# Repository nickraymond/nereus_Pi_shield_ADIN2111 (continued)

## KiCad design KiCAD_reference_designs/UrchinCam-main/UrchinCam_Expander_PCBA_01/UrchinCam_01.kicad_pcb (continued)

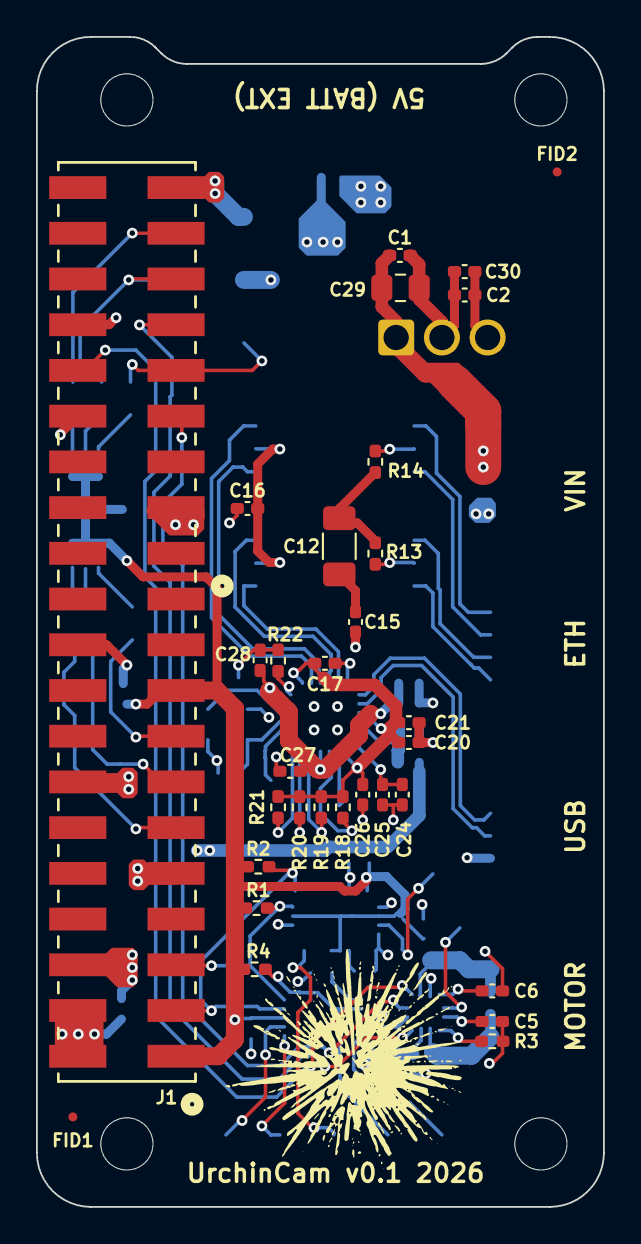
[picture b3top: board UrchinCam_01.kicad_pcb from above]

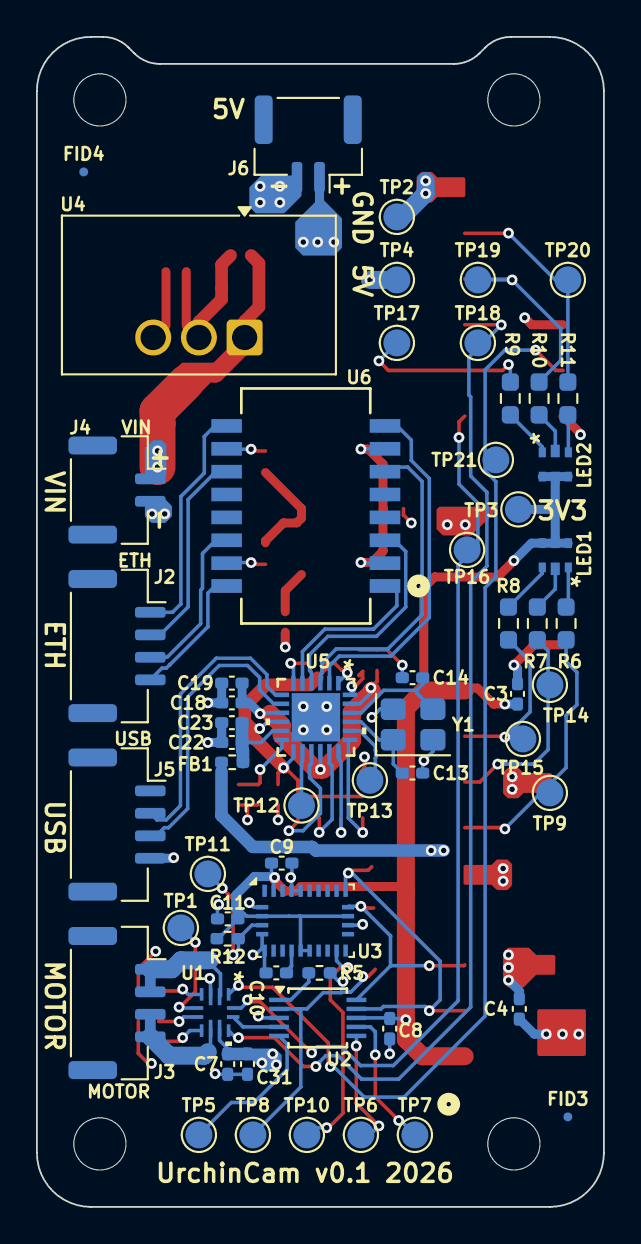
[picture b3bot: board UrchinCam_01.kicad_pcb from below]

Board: 4 copper layers, 31.5 x 65.0 mm, 95 parts (60 on the bottom side), 64 nets.

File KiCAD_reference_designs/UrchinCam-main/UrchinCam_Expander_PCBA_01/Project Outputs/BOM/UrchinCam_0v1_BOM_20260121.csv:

Id,Comment,Designator,Footprint,Quantity,Manufacturer 1,Manufacturer Part Number 1,JLPCB Part Number
1,SM02B-GHS,"J6,J4",JST_GH_SM02B-GHS-TB_1x02-1MP_P1.25mm_Horizontal,2,JST,SM02B-GHS,C189893
2,10uF 50V,C29,C_0805_2012Metric_Pad1.18x1.45mm_HandSolder,1,Murata,GRM21BR61H106KE43L,C440198
3,10uF 10V,"C30,C7",C_0402_1005Metric_Pad0.74x0.62mm_HandSolder,2,Murata,GRM155R61A106ME11D,C408132
4,100nF 50V,"C1,C28,C5,C27,C24,C26,C17,C20,C22,C11,C8,C10,C9,C3,C18,C31,C4",C_0402_1005Metric_Pad0.74x0.62mm_HandSolder,17,Yageo,CC0402KRX5R9BB104,C105882
5,1uF 50V,"C2,C25,C19",C_0402_1005Metric_Pad0.74x0.62mm_HandSolder,3,Taiyo Yuden,UMK105CBJ105MV-F,C2880413
6,TSR 3-2450N,U4,Traco_TSR 3-2450N,1,Traco Power,TSR 3-2450N,C42463890
7,MP6550,U1,MP6550GG,1,Monolithic Power Systems Inc.,MP6550GG,C3681248
8,RTL8152B,U5,RTL8152B,1,Realtek,RTL8152B,C50656
9,2kΩ 1%,R3,R_0402_1005Metric_Pad0.72x0.64mm_HandSolder,1,Vishay Dale,CRCW04022K00FKED,C482125
10,10kΩ 5%,"R2,R21,R19,R1,R18,R20,R4,R5,R12",R_0402_1005Metric_Pad0.72x0.64mm_HandSolder,9,Yageo,RC0402JR-0710KL,C60489
12,75Ω 1%,"R14,R13",R_0402_1005Metric_Pad0.72x0.64mm_HandSolder,2,Yageo,RC0402FR-0775RL,C114757
13,4.7uF 16V,"C21,C23",C_0402_1005Metric_Pad0.74x0.62mm_HandSolder,2,Samsung Electro-Mechanics,CL05A475MO5NUNC,C318563
14,1nF 2kV,C12,C_1206_3216Metric_Pad1.33x1.80mm_HandSolder,1,Samsung Electro-Mechanics,CL31B102KJHNNNE,C16196254
15,470nF 50V,"C15,C6",C_0402_1005Metric_Pad0.74x0.62mm_HandSolder,2,Taiyo Yuden,UMK105ABJ474KV-F,C386109
16,95157-440LF,J1,Amphenol_95157-440LF_2x20_P2.54mm_Vertical,1,Amphenol ICC (FCI),95157-440LF,C5411221
17,10nF 50V,C16,C_0402_1005Metric_Pad0.74x0.62mm_HandSolder,1,Yageo,CC0402KRX7R9BB103,C60133
18,2.49kΩ 1%,R22,R_0402_1005Metric_Pad0.72x0.64mm_HandSolder,1,Vishay Dale,CRCW04022K49FKED,C482132
19,SM04B-GHS,"J2,J3,J5",JST_GH_SM04B-GHS-TB_1x04-1MP_P1.25mm_Horizontal,3,JST,SM04B-GHS,C189895
21,ADS1115IDGS,U2,TSSOP-10_3x3mm_P0.5mm,1,Texas Instruments,ADS1115IDGS,C468683
22,120Ω @ 100MHz,FB1,R_0402_1005Metric_Pad0.72x0.64mm_HandSolder,1,Murata,BLM15PD121SN1D,C76891
23,27pF 50V,"C14,C13",C_0402_1005Metric_Pad0.74x0.62mm_HandSolder,2,Murata,GRM1555C1H270JA01J,C3892269
24,200Ω 1%,"R10,R7",R_0603_1608Metric_Pad0.98x0.95mm_HandSolder,2,Vishay Dale,CRCW0603200RFKEA,C844754
25,91Ω 1%,"R8,R9,R11,R6",R_0603_1608Metric_Pad0.98x0.95mm_HandSolder,4,Yageo,RC0603FR-0791RL,C137670
26,ABM8G-25.000MHZ-18-D2Y-T,Y1,Crystal_SMD_3225-4Pin_3.2x2.5mm,1,Abracon LLC,ABM8G-25.000MHZ-18-D2Y-T,C2939753
27,TS8121CMHF,U6,TS8121CM HF,1,Pulse Electronics,TS8121CM HF,C5718404
28,BNO085,U3,LGA-28_5.2x3.8mm_P0.5mm,1,"CEVA Technologies, Inc.",BNO085,C5189642
29,19-337C/RSBHGHC-A88/4T,"LED2,LED1",19-337C RSBHGHC-A88 4T,2,Everlight Electronics Co Ltd,19-337C/RSBHGHC-A88/4T,C3019536

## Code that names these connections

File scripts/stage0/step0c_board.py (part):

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xp = pin["3"][0] + 0.55
for k in pin: pin[k] = (xp, pin[k][1])
yn = (pin["1"][1] + pin["2"][1]) / 2; yp = (pin["3"][1] + pin["4"][1]) / 2
trk("BM1_N", [pin["1"], pin["2"]], 0.6)
trk("BM1_N", [(xp, yn), (12.2, yn), (12.2 + (5.7 - yn), 5.7), (13.8, 5.7), (15.7, 7.6), (18.1, 7.6)], 2.0)
trk("BM1_N", [(18.1, 7.6), (19.9, 9.4)], 1.6)
trk("BM1_N", [(19.9, 9.4), (21.0, 10.5), (21.0, 12.1)], 2.0)
trk("BM1_P", [pin["3"], pin["4"]], 0.6)
trk("BM1_P", [(xp, yp), (13.8 - (yp - 2.0), yp), (13.8, 2.0)], 2.0)
trk("BM1_P", [(13.8, 2.0), (15.7, 0.1)], 1.4); trk("BM1_P", [(15.7, 0.1), (20.0, 0.1), (21.0, 1.1), (21.0, 3.6)], 2.0)

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ridepos = XY(final["R43"].GetPosition())
put("R43", B_CU, ridepos, (5.0, 0.6, 31.0, 30.0), "ADIN_PWR pull-down: its Pi-board place relative to the block is under the east header's body, so the nearest free place")
r2 = put("R2", (B_CU, F_CU), node19, (5.0, 10.0, 28.0, 30.0), "CFG1 strap resistor, nearest free place to U1 pin 19's via (10.79, 19.34)")
r47 = put("R47", (B_CU, F_CU), node19, (5.0, 10.0, 28.0, 30.0), "ADIN_TIMER resistor, nearest free place to U1 pin 19's via")
put("R37", F_CU, (u10[0], u10[1] + 3.0), (-6.1, 21.5, 5.0, 40.0), "feedback divider, top face north of U10 (C53 stays under U10)")
put("R38", F_CU, (u10[0], u10[1] + 3.0), (-6.1, 21.5, 5.0, 40.0), "feedback divider, top face north of U10")
put("C68", F_CU, c65, WINGN, "1 uF beside C65 at U13")
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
